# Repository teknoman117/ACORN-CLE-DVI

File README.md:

# ACORN-CLE-DVI

Add DVI support to the Acorn CLE-215(+)/101 by using a PI3HDX511D DisplayPort Level Shifter / TMDS Redriver.

The NiteFury, LiteFury, and Acorn CLE-215(+)/101 IO connector has 4x LVDS pairs (2.5V VCCO) and 2x 3.3V differential pairs for a total of 12 IO pins. Since HDMI/DVI requires 4 differential pairs (3 color, 1 clock), we need more 3.3V IO pins than are available. DisplayPort uses LVDS, so there are chips on the market for GPUs and smartphones so that only a single electrical standard is required to be implemented by the ASIC, and an external driver IC can be used.

A boost converter is also present to step the 3.3V supply on the IO connector to 5V to output to the HDMI/DVI sink.

### License

CC-BY-SA 4.0

### Pictures

### Schematic

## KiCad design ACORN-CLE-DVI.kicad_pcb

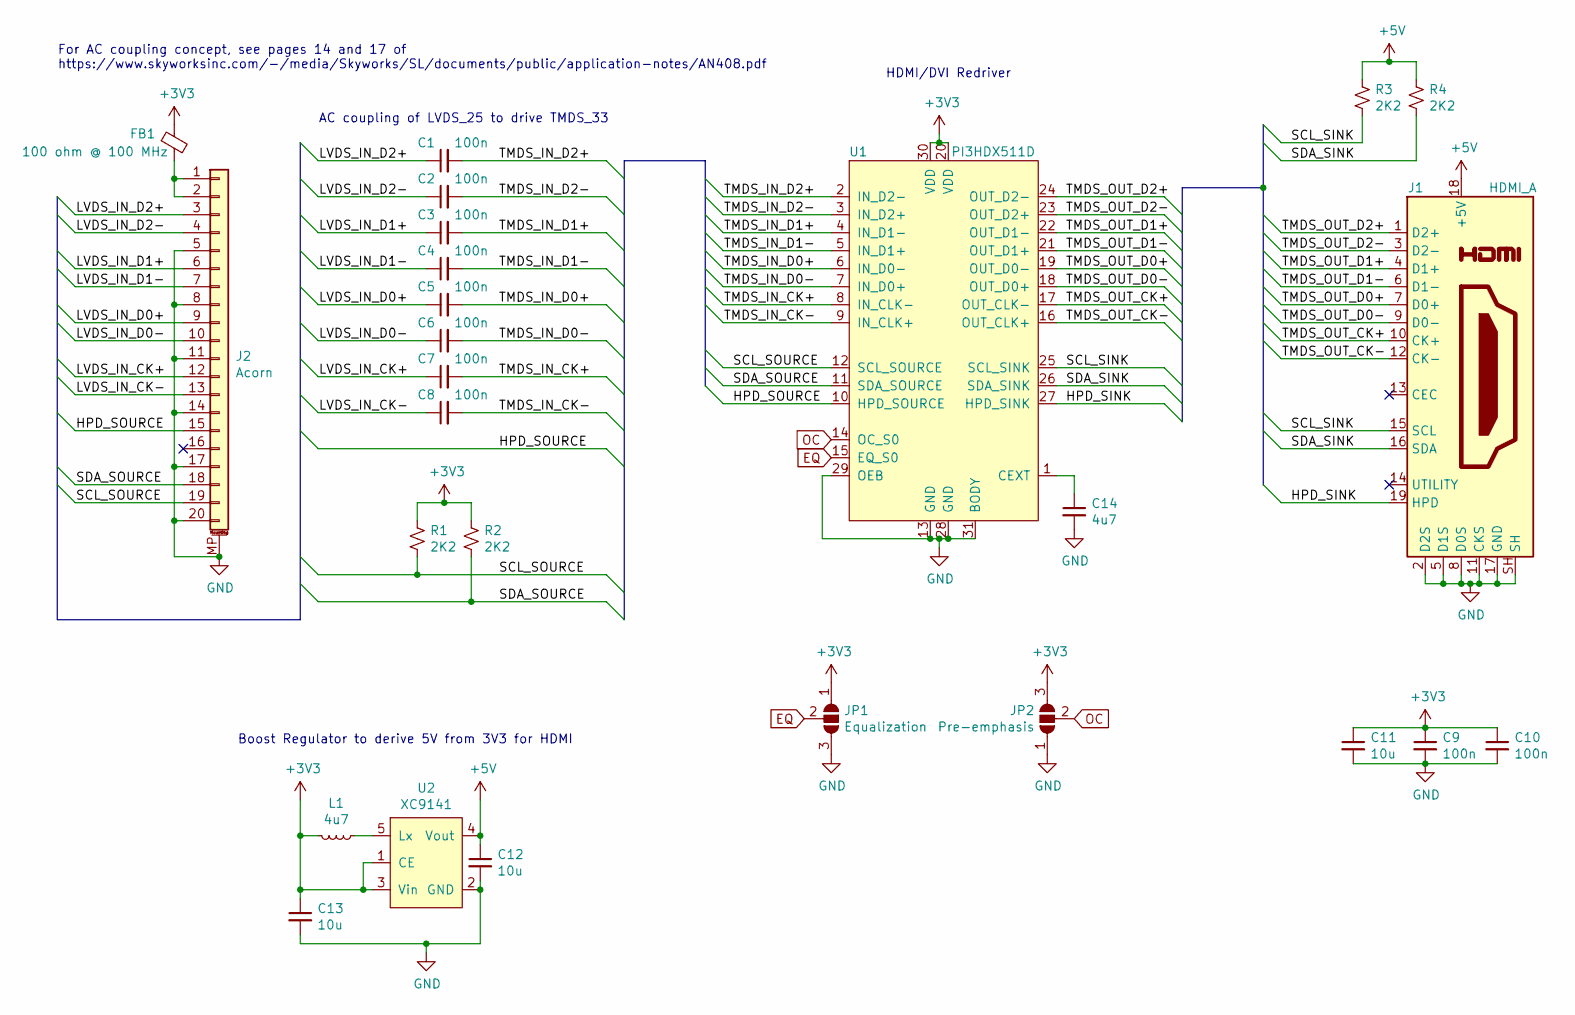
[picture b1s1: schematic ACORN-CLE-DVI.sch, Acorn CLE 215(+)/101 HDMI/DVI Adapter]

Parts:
C1, C2, C3, C4, C5, C6, C7, C8, C9, C10: 100n; C_0402_1005Metric; Digikey_PN 1276-1043-2-ND
C11, C12, C13: 10u; C_0402_1005Metric; Digikey_PN 490-GRM155R61A106ME11DTR-ND
C14: 4u7; C_0402_1005Metric; Digikey_PN 1276-1482-2-ND
FB1: 100 ohm @ 100 MHz; L_0603_1608Metric; Digikey_PN 490-5448-2-ND
J1: HDMI_A; HDMI_A_Female_2000-1-2-41-00-BK; Digikey_PN 1175-1703-ND
J2: Acorn; Hirose_DF52-20S-0.8H_1x20-1MP_P0.80mm_Horizontal; Digikey_PN H125108TR-ND
JP1: Equalization; SolderJumper-3_P1.3mm_Open_RoundedPad1.0x1.5mm_NumberLabels
JP2: Pre-emphasis; SolderJumper-3_P1.3mm_Open_RoundedPad1.0x1.5mm_NumberLabels
L1: 4u7; L_1008_2520Metric; Digikey_PN 535-12797-2-ND
R1, R2, R3, R4: 2K2; R_0402_1005Metric; Digikey_PN 311-2.2KJRTR-ND
U1: PI3HDX511D; TQFN-30; Digikey_PN PI3HDX511DZLEXDITR-ND
U2: XC9141; SOT-23-5; Digikey_PN 893-1369-2-ND

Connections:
+3V3: C9.1, C10.1, C11.1, C13.1, FB1.1, JP1.1 (A), JP2.3 (B), L1.2, R1.1, R2.1, U1.20 (VDD), U1.30 (VDD), U2.1 (CE), U2.3 (Vin)
+5V: C12.1, J1.18 (+5V), R3.1, R4.1, U2.4 (Vout)
/HPD_SINK: J1.19 (HPD), U1.27 (HPD_SINK)
/HPD_SOURCE: J2.15, U1.10 (HPD_SOURCE)
/LVDS_IN_CK+: C7.1, J2.12
/LVDS_IN_CK-: C8.1, J2.13
/LVDS_IN_D0+: C5.1, J2.9
/LVDS_IN_D0-: C6.1, J2.10
/LVDS_IN_D1+: C3.1, J2.6
/LVDS_IN_D1-: C4.1, J2.7
/LVDS_IN_D2+: C1.1, J2.3
/LVDS_IN_D2-: C2.1, J2.4
/SCL_SINK: J1.15 (SCL), R3.2, U1.25 (SCL_SINK)
/SCL_SOURCE: J2.19, R1.2, U1.12 (SCL_SOURCE)
/SDA_SINK: J1.16 (SDA), R4.2, U1.26 (SDA_SINK)
/SDA_SOURCE: J2.18, R2.2, U1.11 (SDA_SOURCE)
/TMDS_IN_CK+: C7.2, U1.8 (IN_CLK-)
/TMDS_IN_CK-: C8.2, U1.9 (IN_CLK+)
/TMDS_IN_D0+: C5.2, U1.6 (IN_D0-)
/TMDS_IN_D0-: C6.2, U1.7 (IN_D0+)
/TMDS_IN_D1+: C3.2, U1.4 (IN_D1-)
/TMDS_IN_D1-: C4.2, U1.5 (IN_D1+)
/TMDS_IN_D2+: C1.2, U1.2 (IN_D2-)
/TMDS_IN_D2-: C2.2, U1.3 (IN_D2+)
/TMDS_OUT_CK+: J1.10 (CK+), U1.17 (OUT_CLK-)
/TMDS_OUT_CK-: J1.12 (CK-), U1.16 (OUT_CLK+)
/TMDS_OUT_D0+: J1.7 (D0+), U1.19 (OUT_D0-)
/TMDS_OUT_D0-: J1.9 (D0-), U1.18 (OUT_D0+)
/TMDS_OUT_D1+: J1.4 (D1+), U1.22 (OUT_D1-)
/TMDS_OUT_D1-: J1.6 (D1-), U1.21 (OUT_D1+)
/TMDS_OUT_D2+: J1.1 (D2+), U1.24 (OUT_D2-)
/TMDS_OUT_D2-: J1.3 (D2-), U1.23 (OUT_D2+)
EQ: JP1.2 (C), U1.15 (EQ_S0)
GND: C9.2, C10.2, C11.2, C12.2, C13.2, C14.2, J1.2 (D2S), J1.5 (D1S), J1.8 (D0S), J1.11 (CKS), J1.17 (GND), J1.SH, J2.5, J2.8, J2.11, J2.14, J2.17, J2.20, J2.MP (MountPin), JP1.3 (B), JP2.1 (A), U1.13 (GND), U1.28 (GND), U1.29 (OEB), U1.31 (BODY), U2.2 (GND)
unnamed: C14.1, U1.1 (CEXT)
unnamed: FB1.2, J2.1, J2.2
unnamed: L1.1, U2.5 (Lx)
OC: JP2.2 (C), U1.14 (OC_S0)

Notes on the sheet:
AC coupling of LVDS_25 to drive TMDS_33
For AC coupling concept, see pages 14 and 17 of https://www.skyworksinc.com/-/media/Skyworks/SL/documents/public/application-notes/AN408.pdf
HDMI/DVI Redriver
Boost Regulator to derive 5V from 3V3 for HDMI

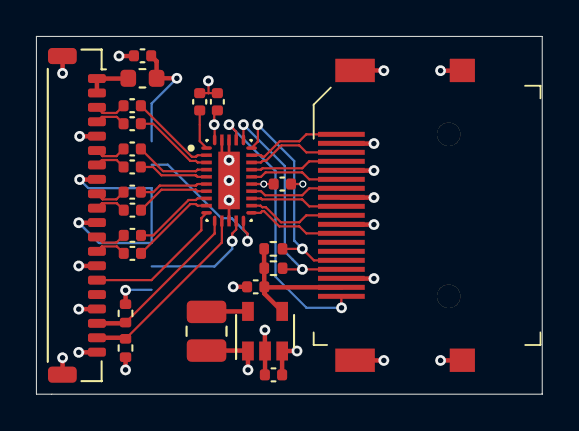
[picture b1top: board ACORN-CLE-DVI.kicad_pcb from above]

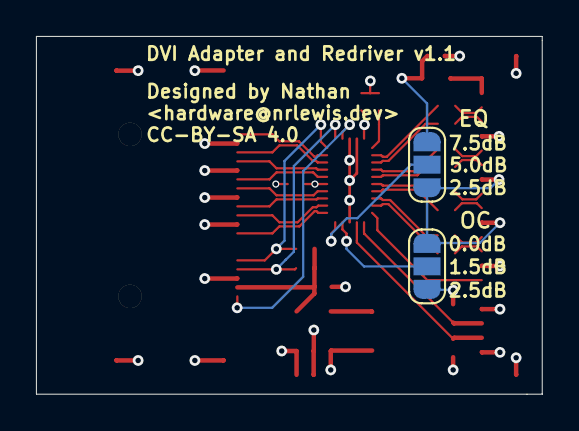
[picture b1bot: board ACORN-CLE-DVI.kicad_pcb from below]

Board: 4 copper layers, 28.1 x 19.9 mm, 26 parts (2 on the bottom side), 38 nets.

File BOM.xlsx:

Reference | Quantity | Value | Footprint | Datasheet | Digikey_Link | Digikey_PN
C1 C2 C3 C4 C5 C6 C7 C8 C9 C10 | 10 | 100n | Capacitor_SMD:C_0402_1005Metric | https://media.digikey.com/pdf/Data%20Sheets/Samsung%20PDFs/C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 | https://www.digikey.com/en/products/detail/samsung-electro-m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 | 1276-1043-2-ND
C11 C12 C13 | 3 | 10u | Capacitor_SMD:C_0402_1005Metric | https://www.murata.com/-/media/webrenewal/support/library/ca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 | https://www.digikey.com/en/products/detail/murata-electronic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 | 490-GRM155R61A106ME11DTR-ND
C14 | 1 | 4u7 | Capacitor_SMD:C_0402_1005Metric | http://www.samsungsem.com/kr/support/product-search/mlcc/CL0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 | https://www.digikey.com/en/products/detail/samsung-electro-m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 | 1276-1482-2-ND
FB1 | 1 | 100 ohm @ 100 MHz | Inductor_SMD:L_0603_1608Metric | https://media.digikey.com/pdf/Data%20Sheets/Murata%20PDFs/BL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 | https://www.digikey.com/en/products/detail/murata-electronic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 | 490-5448-2-ND
J1 | 1 | HDMI_A | Digikey:HDMI_A_Female_2000-1-2-41-00-BK | http://www.cnctech.us/pdfs/2000-1-2-41-00-BK.pdf | https://www.digikey.com/en/products/detail/cnc-tech/2000-1-2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 | 1175-1703-ND
J2 | 1 | Acorn | ACORN-CLE-HDMI:Hirose_DF52-20S-0.8H_1x20-1MP_P0.80mm_Horizontal | https://www.hirose.com/product/document?clcode=&productname=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 | https://www.digikey.com/en/products/detail/hirose-electric-c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 | H125108TR-ND
L1 | 1 | 4u7 | Inductor_SMD:L_1008_2520Metric | https://abracon.com/Magnetics/inductors/AIML-1008HC.pdf | https://www.digikey.com/en/products/detail/abracon-llc/AIML-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 | 535-12797-2-ND
R1 R2 R3 R4 | 4 | 2K2 | Resistor_SMD:R_0402_1005Metric | https://www.yageo.com/upload/media/product/productsearch/dat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 | https://www.digikey.com/en/products/detail/yageo/RC0402JR-07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 | 311-2.2KJRTR-ND
U1 | 1 | PI3HDX511D | ACORN-CLE-HDMI:TQFN-30 | https://www.mouser.com/datasheet/2/115/diodes_inc_diod-s-a00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 | https://www.digikey.com/en/products/detail/diodes-incorporat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 | PI3HDX511DZLEXDITR-ND
U2 | 1 | XC9141 | Package_TO_SOT_SMD:SOT-23-5 | https://www.torexsemi.com/file/xc9141/XC9141-XC9142.pdf | https://www.digikey.com/en/products/detail/torex-semiconduct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 | 893-1369-2-ND

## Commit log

2021-09-10 first commit, why are differential signals so damn stupid
2021-09-10 Add README.md
2021-09-10 routed differential pairs
2021-09-11 schematic done, most of board routing
2021-09-11 license under CC-BY-SA 4.0
2021-09-12 functionally complete, need to verify before buying
2021-09-13 add datasheets and digikey part numbers
2021-09-13 correct the size of the TQFN-30 footprint
2021-09-13 state at manufacturing
2021-09-18 add schematic picture
2021-09-29 add pictured of assembled board
2021-09-29 add sample vivado project
2021-09-30 set pad size for TQFN to exact recommended layout, widen differential traces at redriver
2021-09-30 move all capacitors to top layer
